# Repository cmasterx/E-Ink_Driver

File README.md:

# E-Ink_Driver
Test PCB and firmware for E-Ink display

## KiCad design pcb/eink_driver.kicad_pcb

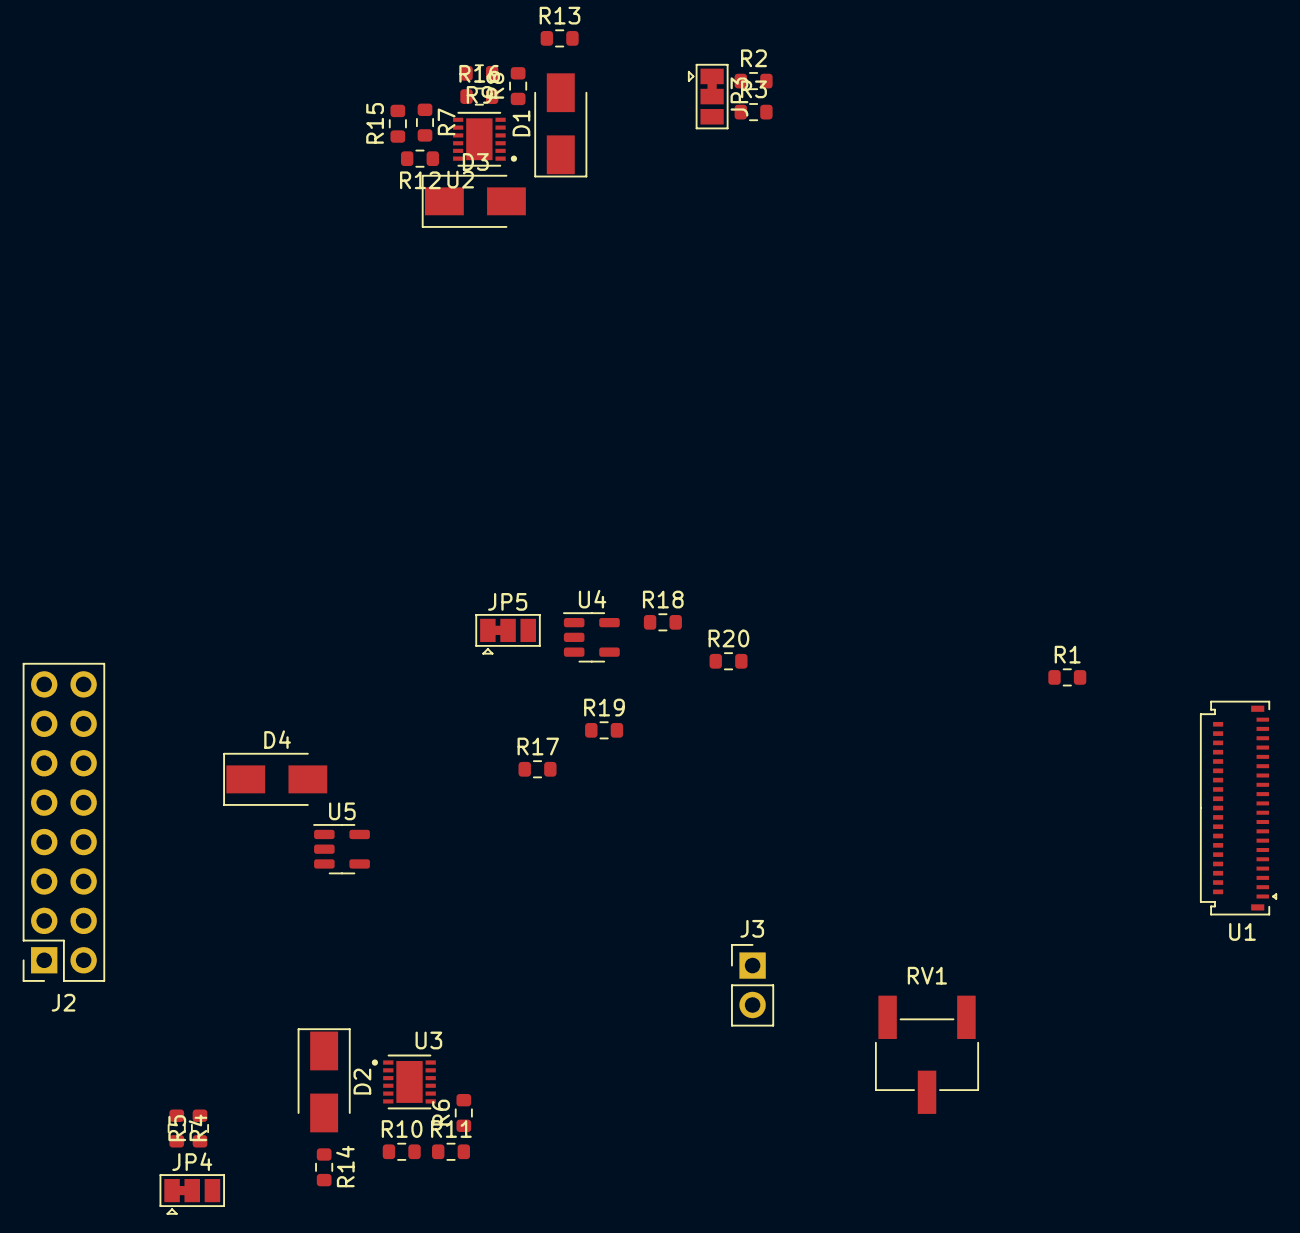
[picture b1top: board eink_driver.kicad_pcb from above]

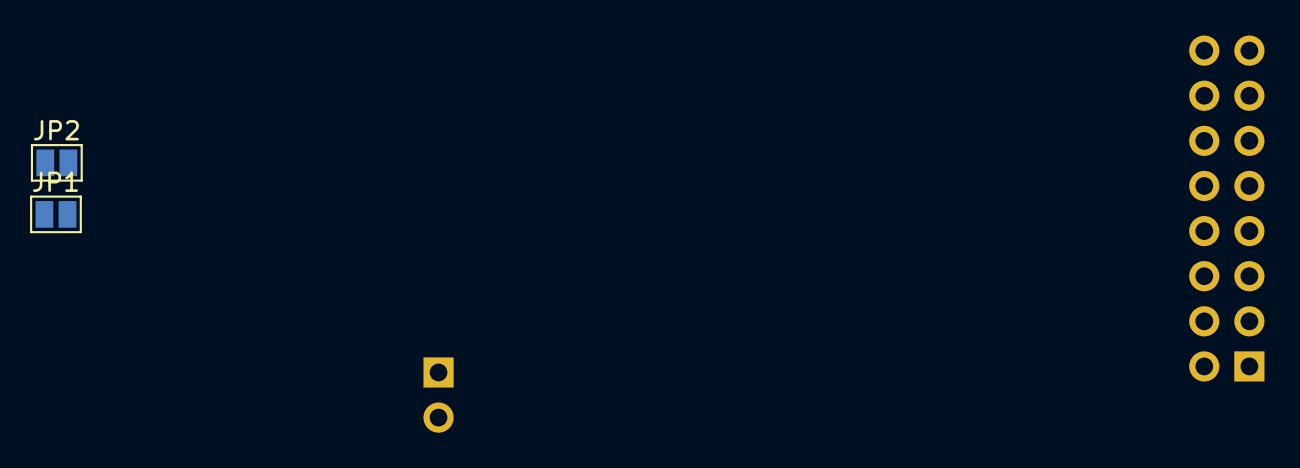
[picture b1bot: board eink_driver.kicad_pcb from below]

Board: 4 copper layers, 37 parts (2 on the bottom side), 38 nets, no tracks yet.

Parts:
D1, D2, D3, D4: D_Schottky; D_SMA
J2: Conn_02x08_Counter_Clockwise; PinSocket_2x08_P2.54mm_Vertical
J3: 3.3V Jumper; PinHeader_1x02_P2.54mm_Vertical
JP1: P10 NC; SolderJumper-2_P1.3mm_Open_Pad1.0x1.5mm
JP2: P9 NC; SolderJumper-2_P1.3mm_Open_Pad1.0x1.5mm
JP3, JP4, JP5: SolderJumper_3_Bridged12; SolderJumper-3_P1.3mm_Bridged12_Pad1.0x1.5mm
R1, R2, R3, R4, R5, R15, R17, R18: 10k; R_0603_1608Metric
R6: 12k; R_0603_1608Metric
R7: 140k; R_0603_1608Metric
R8, R9, R10, R11: 100k; R_0603_1608Metric
R12, R13, R14: 1k; R_0603_1608Metric
R16: 16k; R_0603_1608Metric
R19: 83k; R_0603_1608Metric
R20: 5k; R_0603_1608Metric
RV1: 10k; Potentiometer_Bourns_3269W_Vertical
U1: ED060SC4; Molex_502250-3991_2Rows-39Pins-1MP_P0.60mm_Horizontal
U2, U3: R1283x; SON50P300X270X60-13N
U4: LM2611xMF; SOT-23-5
U5: AP3012; SOT-23-5

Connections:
+3V3: J3.1, JP1.1 (A), U1.4 (VDD), U1.8 (SHR), U1.30 (U1CE2), U1.35 (U2CE2), U1.36 (U2CE1)
+15V: D3.1 (K), R7.1, R12.1, U1.2 (VPOS)
+22V: D4.1 (K), R19.1, U1.23 (GVDD)
-15V: D1.2 (A), R1.1, R8.1, R13.1, U1.1 (VNEG), U2.4 (V_{OUTN})
-20V: D2.2 (A), R10.1, R14.1, U1.24 (GVEE), U3.4 (V_{OUTN})
CKV: J2.7, U1.33 (U1CKV), U1.38 (U2CKV)
CL: J2.1, U1.5 (CL)
GMODE: J2.5, U1.27 (GMODE2), U1.28 (GMODE1)
GND: J2.8, JP2.1 (A), R3.2, R5.2, R15.2, R18.2, R20.2, RV1.2, U1.3 (VSS), U1.29 (RL), U1.31 (U1CE1), U1.34 (VBORDER), U2.12 (PGND), U5.2 (GND)
LE: J2.2, U1.6 (LE)
unnamed: R16.1, U2.7 (V_{REF})
unnamed: R6.2, U3.7 (V_{REF})
unnamed: R7.2, R15.1, U2.9 (V_{FB1})
unnamed: R9.2, R16.2, U2.6 (V_{FB2})
unnamed: R6.1, R11.2, U3.6 (V_{FB2})
unnamed: D1.1 (K), U2.3 (L_{X2})
unnamed: D2.1 (K), U3.3 (L_{X2})
unnamed: D3.2 (A), U2.2 (L_{x1})
unnamed: D4.2 (A), U5.1 (SW)
unnamed: JP1.2 (B), U1.10 (NC)
unnamed: JP2.2 (B), U1.9 (NC)
unnamed: JP3.1 (A), R2.2
unnamed: JP3.2 (C), U2.5 (CE)
unnamed: JP3.3 (B), R3.1
unnamed: JP4.1 (A), R4.2
unnamed: JP4.2 (C), U3.5 (CE)
unnamed: JP4.3 (B), R5.1
unnamed: JP5.1 (A), R17.2
unnamed: JP5.2 (C), U5.4 (~SHDN)
unnamed: JP5.3 (B), R18.1
unnamed: R1.2, RV1.1, U1.22 (VCOM)
unnamed: R8.2, R9.1
unnamed: R10.2, R11.1
unnamed: R19.2, R20.1, U5.3 (FB)
OE: J2.3, U1.7 (OE)
SPH: J2.4, U1.11 (SPH)
SPV: J2.6, U1.32 (U1SPV), U1.37 (U2SPV)
VDD: R2.1, R4.1, R17.1, U2.8 (V_{CC}), U2.11 (PV_{cc}), U3.8 (V_{CC}), U3.11 (PV_{cc}), U5.5 (IN)

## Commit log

2022-08-22 Add ATL KiCAD library
2022-08-22 Switch ATL KiCAD library to use dev branch
2022-08-22 Setup initial configurations for KiCAD project
2023-01-03 Progress
2023-01-07 Tied physical components to layout components and created initial pcb file
